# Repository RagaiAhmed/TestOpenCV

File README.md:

# TestOpenCV
## Open CV
*First we read the image and put it in variable **img** then we reduce it's size by 60% in order to see the whole picture as in it's normal size we can't see the name and color of some shapes.*

*Then we assign the image again in variable **img** after resizing it.*

*We convert  BGR image to HSV and assign the result in **hsv** then we threshold the hsv image for the range of the colores that we want to trace then we but the resulted images in variable **mask\#**.*

*Each **mask** hold hsv image with specific range of color.*

*Then we put the mask's variables and the colores of shapes in two different lists.*

*Inside for loop that loop over the masks the contour start to countor each image of the masks and then another for loop start to loop over the contours and check inside it the coordinates of the contours of each single shape in order to print the name of the shape.*

*Also we print the color of each shape as the color list is looped with the mask list.*

*We finally print the image with the shapes and colores.*

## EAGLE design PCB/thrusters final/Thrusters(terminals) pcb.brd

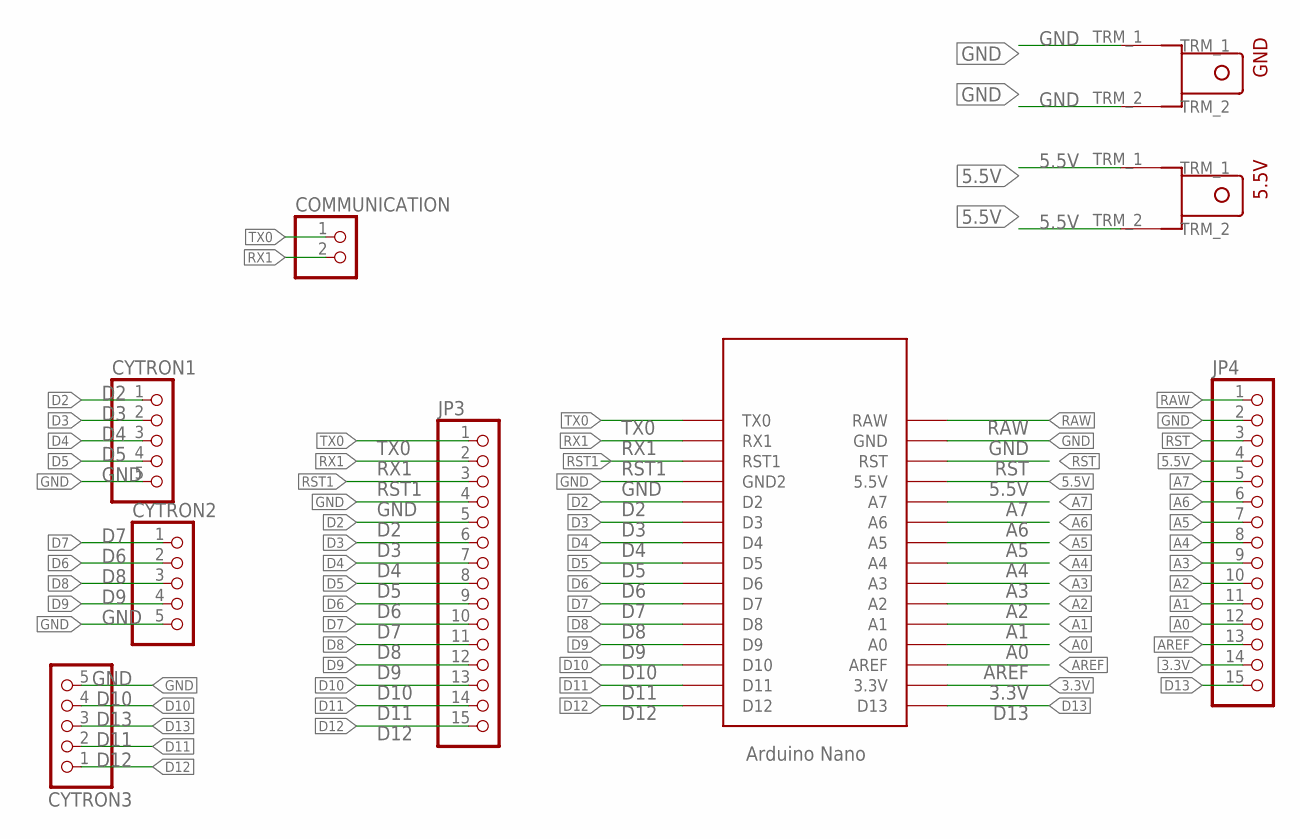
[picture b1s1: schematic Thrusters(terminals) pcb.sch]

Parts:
5.5V: TERMINAL_EDITED
COMMUNICATION: PINHD-2_DATA; 1X02_DATA
CYTRON1, CYTRON2, CYTRON3: PINHD-5_DATA; 1X05_DATA
GND: TERMINAL_EDITED
JP3, JP4: PINHD-1X15; 1X15
U$1: ARDUINO_NANO; NANO

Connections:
3.3V: JP4.14, U$1.3.3V
5.5V: 5.5V.TRM_1, 5.5V.TRM_2, JP4.4, U$1.5V (5.5V)
A0: JP4.12, U$1.A0
A1: JP4.11, U$1.A1
A2: JP4.10, U$1.A2
A3: JP4.9, U$1.A3
A4: JP4.8, U$1.A4
A5: JP4.7, U$1.A5
A6: JP4.6, U$1.A6
A7: JP4.5, U$1.A7
AREF: JP4.13, U$1.AREF
D2: CYTRON1.1, JP3.5, U$1.D2
D3: CYTRON1.2, JP3.6, U$1.D3
D4: CYTRON1.3, JP3.7, U$1.D4
D5: CYTRON1.4, JP3.8, U$1.D5
D6: CYTRON2.2, JP3.9, U$1.D6
D7: CYTRON2.1, JP3.10, U$1.D7
D8: CYTRON2.3, JP3.11, U$1.D8
D9: CYTRON2.4, JP3.12, U$1.D9
D10: CYTRON3.4, JP3.13, U$1.D10
D11: CYTRON3.2, JP3.14, U$1.D11
D12: CYTRON3.1, JP3.15, U$1.D12
D13: CYTRON3.3, JP4.15, U$1.D13
GND: CYTRON1.5, CYTRON2.5, CYTRON3.5, GND.TRM_1, GND.TRM_2, JP3.4, JP4.2, U$1.GND, U$1.GND1 (GND2)
RAW: JP4.1, U$1.RAW
RST: JP4.3, U$1.RST
RST1: JP3.3, U$1.RST1
RX1: COMMUNICATION.2, JP3.2, U$1.RX1
TX0: COMMUNICATION.1, JP3.1, U$1.TX0

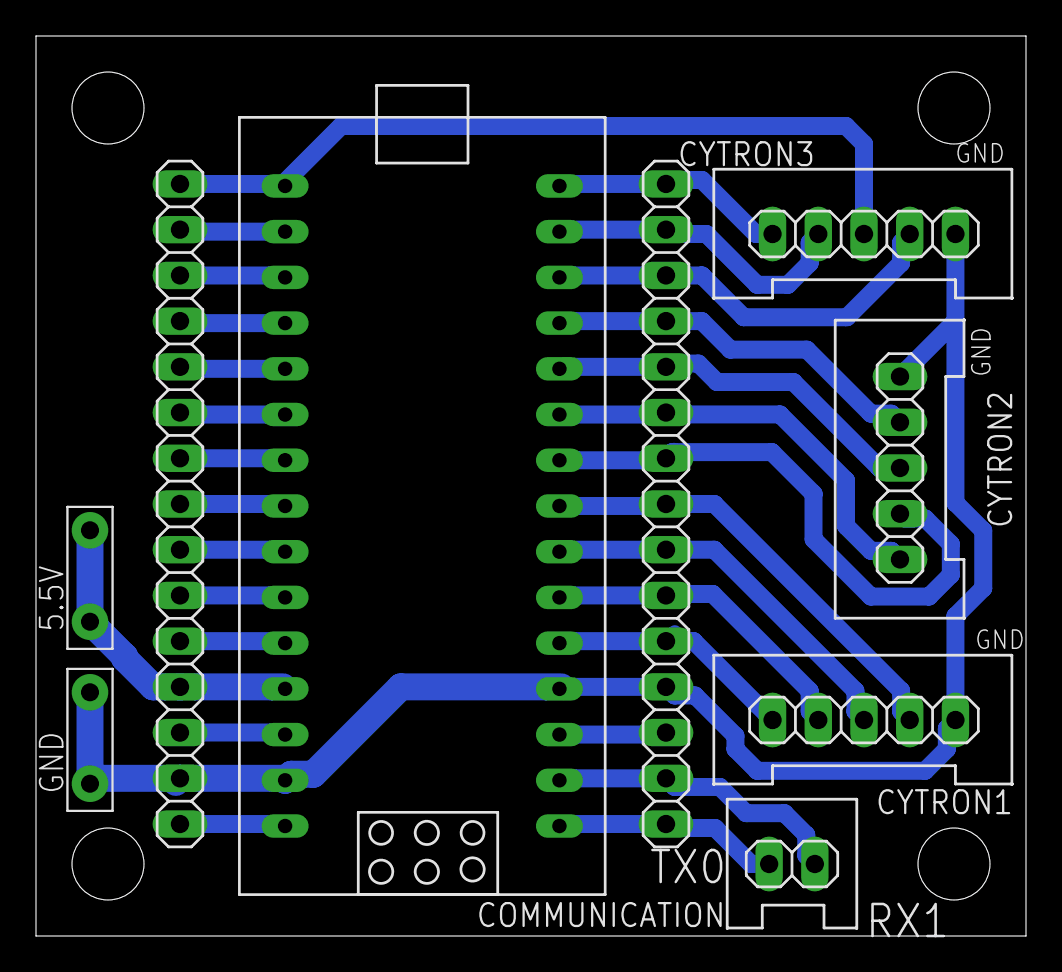
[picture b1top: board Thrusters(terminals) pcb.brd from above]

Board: 2 copper layers, 55.0 x 50.0 mm, 9 parts (0 on the bottom side), 29 nets.

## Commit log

2021-10-17 ctrated the shape detection script and the output images are saved in the Examoles folder
2021-10-18 Added another version if the code and edited the cv file with the first vesrion
2021-10-18 Added Examples in the path of the images
2021-10-19 Update cv.py
    I treated the black rectangles as if they are borders
2021-10-19 Initial change
    Example code edited resize and threshold
2021-10-19 Add files via upload
    Task 1: LED controller using Arduino and QT IDE.
    This task includes: QT communication with Arduino via QSerialPort + QT GUI basics.
2021-10-19 arduino code and the qt code
2021-10-19 qt file created
2021-10-19 qt- design is created, on functionality is checked
2021-10-19 ardino logic added
2021-10-19 Size control
    to avoid big polygons to be detected used contourarea to control it
2021-10-19 Add files via upload
    Added the main.py OpenCV task
2021-10-19 Add files via upload
    Added example of output of my OpenCv program to the input test1
2021-10-19 qt-serial port configration added
2021-10-19 Update main.py
    Removed a debugging print statement
2021-10-19 deleted black and white image
2021-10-19 qt- control logic added + some modifications to arduio code
2021-10-20 Arduino- there were some problms when using delay, now another approch is used and everything works fine
2021-10-20 Qt GUI
2021-10-20 updated the arduino
    - Changed the loop and setup functions.
    - added the serial and blinking code
2021-10-20 remove contours
2021-10-20 Revert "remove contours"
    This reverts commit 64041b230acefbdcafdba012b538a37dc470f235.
2021-10-20 add qt
2021-10-20 put example
2021-10-20 all without imports
2021-10-20 Add imoprts
2021-10-20 change test
2021-10-20 Change scale
2021-10-20 opencs- color detection added
2021-10-20 Serial GUI
2021-10-21 Qt Task
2021-10-21 add Qt project
2021-10-22 changed values of threshold
2021-10-23 Color detection
    used contour detection for every color then added each arr of contours to one full arr then detected the shape and added the colors in respect to order
2021-10-23 Revert "Youssef"
2021-10-23 edit for the arduino code
2021-10-23 Create QT documentation
2021-10-23 Create Shape and color detection
2021-10-23 Rename Blinking_LED.pro to QT/Blinking_LED.pro
2021-10-23 Rename Blinking_LED.pro.user to QT/Blinking_LED.pro.user
2021-10-23 Rename Dialog.cpp to QT/Dialog.cpp
2021-10-23 Rename main.cpp to QT/main.cpp
2021-10-23 Rename mainwindow.h to QT/mainwindow.h
2021-10-23 Rename mainwindow.ui to QT/mainwindow.ui
2021-10-23 Create open cv documentation
2021-10-23 Rename cv.py to Shape and color detection/cv.py
2021-10-23 Adding two simultaneous blinks
2021-10-23 Update arduino.ino
    - Added code necessary for the two LEDs to blink.
2021-10-23 README.md added
2021-10-23 low_level_image_shape_detection.ipynb added
2021-10-23 added some notebook comments in README.md
2021-10-23 Create Arduino documentation
2021-10-24 Add Task one solution
2021-10-24 Update qtserialport.ino
    update arduino code to solve conflicts
2021-10-24 add qt files
2021-11-04 thrusters pcb and sticker with printed pdf
2021-11-08 thrusters pcb
